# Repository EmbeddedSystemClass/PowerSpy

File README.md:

# PowerSpy

PowerSpy is an IoT device for non-invasive two-phases energy monitoring.

## Features
##### Controller Device / [SoC ESP32 with Xtensa® Dual-Core 32-bit LX6 MPU, Bluetooth 4.2 and Wi-Fi](https://www.espressif.com/sites/default/files/documentation/esp32_datasheet_en.pdf)

##### Low Power Requirements / Does not apply in this project

##### Hardware Project / [Autodesk EAGLE](https://www.autodesk.com/products/eagle/free-download)

##### Firmware Project / [Eclipse IDE](https://www.eclipse.org/eclipseide/)

##### 3D Model Project / [Autodesk Fusion 360](https://www.autodesk.com/products/fusion-360/overview#banner)

## PCB Details

## How to Connect

## Schematic

### Contributing
0. Give this project a :star:
1. Create an issue and describe your idea.
2. [Fork it](https://github.com/TiagoPaulaSilva/PowerSpy/fork).
3. Create your feature branch (`git checkout -b my-new-feature`).
4. Commit your changes (`git commit -a -m "Added feature title"`).
5. Publish the branch (`git push origin my-new-feature`).
6. Create a new pull request.
7. Done! :heavy_check_mark:

### License Information
<br /><span xmlns:dct="http://purl.org/dc/terms/" property="dct:title">PowerSpy</span> by <a xmlns:cc="http://creativecommons.org/ns#" href="https://github.com/TiagoPaulaSilva" property="cc:attributionName" rel="cc:attributionURL">Tiago Silva</a> is licensed under a <a rel="license" href="http://creativecommons.org/licenses/by-sa/4.0/">Creative Commons Attribution-ShareAlike 4.0 International License</a>.<br />Permissions beyond the scope of this license may be available at <a xmlns:cc="http://creativecommons.org/ns#" href="https://twitter.com/tiagopsilvaa" rel="cc:morePermissions">tiagodepaulasilva@gmail.com</a>.

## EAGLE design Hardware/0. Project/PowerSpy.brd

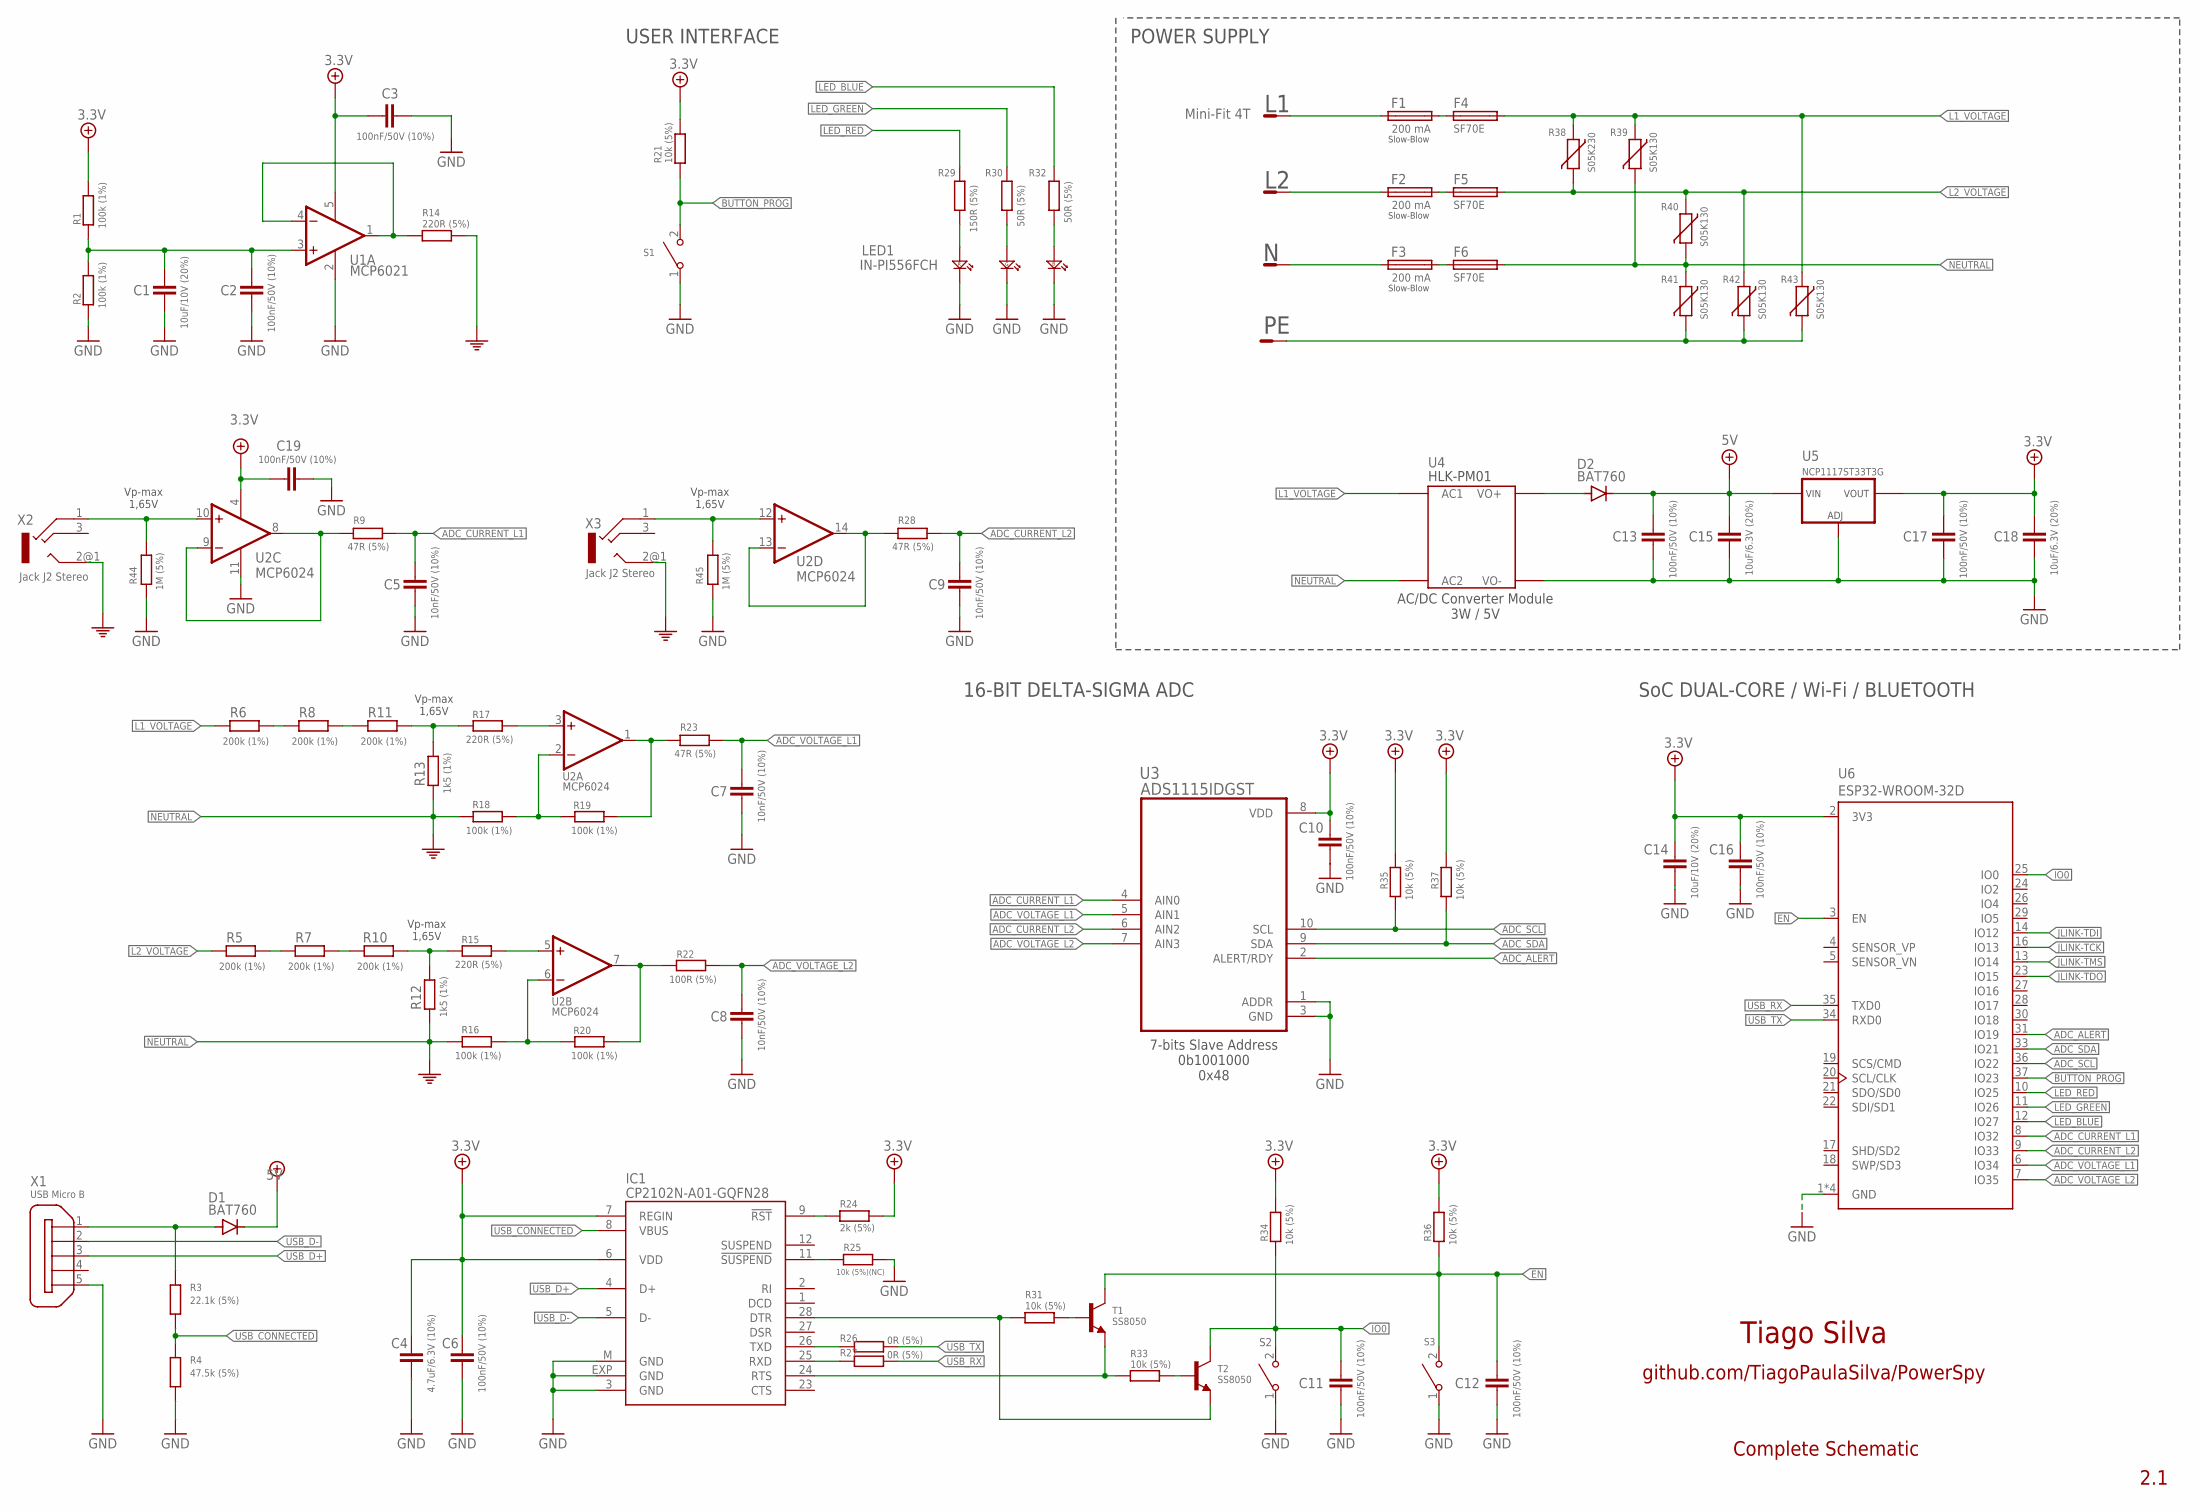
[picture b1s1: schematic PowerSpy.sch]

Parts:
C1, C14: 10uF/10V (20%); C0603K
C2, C3, C6, C10, C11, C12, C13, C16, C17, C19: 100nF/50V (10%); C0603K
C4: 4.7uF/6.3V (10%); C0603K
C5, C7, C8, C9: 10nF/50V (10%); C0603K
C15, C18: 10uF/6.3V (20%); C0603K
CN1: Mini-Fit 4T; 39-30-?04?
D1, D2: BAT760; SOD323-W
F1, F2, F3: 200 mA; QPL
F4, F5, F6: SF70E; LITTLEFUSE
IC1: CP2102N-A01-GQFN28; MLP28
LED1: IN-PI556FCH; INPI556FCH
R1, R2, R16, R18, R19, R20: 100k (1%); R0603
R3: 22.1k (5%); R0603
R4: 47.5k (5%); R0603
R5, R6, R7, R8, R10, R11: 200k (1%); R0603
R9, R23, R28: 47R (5%); R0603
R12, R13: 1k5 (1%); R0603
R14, R15, R17: 220R (5%); R0603
R21, R31, R33, R34, R35, R36, R37: 10k (5%); R0603
R22: 100R (5%); R0603
R24: 2k (5%); R0603
R25: 10k (5%)(NC); R0603
R26, R27: 0R (5%); R0603
R29: 150R (5%); R0603
R30, R32: 50R (5%); R0603
R38: S05K230; S05K11
R39, R40, R41, R42, R43: S05K130; S05K11
R44, R45: 1M (5%); R0603
S1, S2, S3: TL3302AF180QG; 434121050816
T1, T2: SS8050; SOT23
U1: MCP6021; SOT23-5
U2: MCP6024; 14-SOIC
U3: ADS1115IDGST; SOP50P490X110-10N
U4: HLK-PM01
U5: NCP1117ST33T3G; SOT223
U6: ESP32-WROOM-32D; MODULE_ESP32-WROOM-32D
X1: USB Micro B; ZX62D-B-5PA8
X2, X3: Jack J2 Stereo; 1503_07

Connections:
3.3V: C4.1, C6.1, C10.1, C14.1, C16.1, C17.1, C18.1, IC1.6 (VDD), IC1.7 (REGIN), R1.1, R21.1, R24.2, R34.1, R35.1, R36.1, R37.1, U3.8 (VDD), U5.2 (VOUT), U5.4 (VOUT), U6.2 (3V3)
5V: C13.1, C15.1, D1.C, D2.C, U5.3 (VIN)
+4.1V: C3.1, C19.1, U1.5 (V+), U2.4 (V+)
ADC_ALERT: U3.2 (ALERT/RDY), U6.31 (IO19)
ADC_CURRENT_L1: C5.1, R9.1, U3.4 (AIN0), U6.8 (IO32)
ADC_CURRENT_L2: C9.1, R28.1, U3.6 (AIN2), U6.9 (IO33)
ADC_SCL: R35.2, U3.10 (SCL), U6.36 (IO22)
ADC_SDA: R37.2, U3.9 (SDA), U6.33 (IO21)
ADC_VOLTAGE_L1: C7.1, R23.1, U3.5 (AIN1), U6.6 (IO34)
ADC_VOLTAGE_L2: C8.1, R22.1, U3.7 (AIN3), U6.7 (IO35)
BUTTON_PROG: R21.2, S1.2, U6.37 (IO23)
DTR: IC1.28 (DTR), R31.2, T2.2 (E)
EN: C12.1, R36.2, S3.2, T1.3 (C), U6.3 (EN)
GND: C1.2, C2.2, C3.2, C4.2, C5.2, C6.2, C7.2, C8.2, C9.2, C10.2, C11.2, C12.2, C13.2, C14.2, C15.2, C16.2, C17.2, C18.2, C19.2, IC1.3 (GND), IC1.EXP (GND), IC1.M (GND), LED1.4 (KB4), LED1.5 (KG6), LED1.6 (KR5), R2.2, R4.1, R25.1, R44.2, R45.2, S1.1, S2.1, S3.1, U1.2 (V-), U2.11 (V-), U3.1 (ADDR), U3.3 (GND), U4.P$3 (VO-), U5.1 (GND), U6.1 (GND), U6.15 (GND), U6.38 (GND), U6.39 (GND), X1.5
IO0: C11.1, R34.2, S2.2, T2.3 (C), U6.25 (IO0)
JLINK-TCK: U6.16 (IO13)
JLINK-TDI: U6.14 (IO12)
JLINK-TDO: U6.23 (IO15)
JLINK-TMS: U6.13 (IO14)
L1_VOLTAGE: F4.2, R6.1, R38.1, R39.1, R43.1, U4.P$1 (AC1)
L2_VOLTAGE: F5.2, R5.1, R38.2, R40.1, R42.1
LED_BLUE: R32.1, U6.12 (IO27)
LED_GREEN: R30.1, U6.11 (IO26)
LED_RED: R29.1, U6.10 (IO25)
unnamed: IC1.11 (!SUSPEND), R25.2
unnamed: IC1.9 (!RST), R24.1
unnamed: LED1.2 (AR2), R29.2
unnamed: F1.1, F4.1
unnamed: R33.1, T2.1 (B)
unnamed: D2.A, U4.P$4 (VO+)
unnamed: R31.1, T1.1 (B)
unnamed: IC1.26 (TXD), R26.2
unnamed: F2.1, F5.1
unnamed: IC1.25 (RXD), R27.2
unnamed: R9.2, U2.8 (OUT), U2.9 (-IN)
unnamed: R8.2, R11.1
unnamed: R14.2, U1.1 (OUT), U1.4 (-IN)
unnamed: C1.1, C2.1, R1.2, R2.1, U1.3 (+IN)
unnamed: R19.1, R23.2, U2.1 (OUT)
unnamed: R10.2, R12.1, R15.2
unnamed: F3.1, F6.1
unnamed: CN1.4, R41.2, R42.2, R43.2
unnamed: R6.2, R8.1
unnamed: R20.1, R22.2, U2.7 (OUT)
unnamed: LED1.1 (AG1), R30.2
unnamed: R28.2, U2.13 (-IN), U2.14 (OUT)
unnamed: CN1.1, F1.2
unnamed: CN1.2, F2.2
unnamed: CN1.3, F3.2
unnamed: LED1.3 (AB3), R32.2
unnamed: R7.2, R10.1
unnamed: R5.2, R7.1
unnamed: R18.1, R19.2, U2.2 (-IN)
unnamed: R11.2, R13.1, R17.2
unnamed: R17.1, U2.3 (+IN)
unnamed: R16.1, R20.2, U2.6 (-IN)
unnamed: R15.1, U2.5 (+IN)
unnamed: R44.1, U2.10 (+IN), X2.1
unnamed: R45.1, U2.12 (+IN), X3.1
NEUTRAL: F6.2, R12.2, R13.2, R14.1, R16.2, R18.2, R39.2, R40.2, R41.1, U4.P$2 (AC2), X3.2@1 (2)
PE: X2.2@1 (2)
RTS: IC1.24 (RTS), R33.2, T1.2 (E)
USB_CONNECTED: IC1.8 (VBUS), R3.1, R4.2
USB_D+: IC1.4 (D+), X1.3
USB_D-: IC1.5 (D-), X1.2
USB_RX: R27.1, U6.35 (TXD0)
USB_TX: R26.1, U6.34 (RXD0)
VUSB: D1.A, R3.2, X1.1

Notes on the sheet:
Tiago Silva
github.com/TiagoPaulaSilva/PowerSpy
2.1
Complete Schematic
AC/DC Converter Module 3W / 5V
POWER SUPPLY
Slow-Blow
16-BIT DELTA-SIGMA ADC
SoC DUAL-CORE / Wi-Fi / BLUETOOTH
USER INTERFACE
Vp-max 1,65V
7-bits Slave Address 0b1001000 0x48

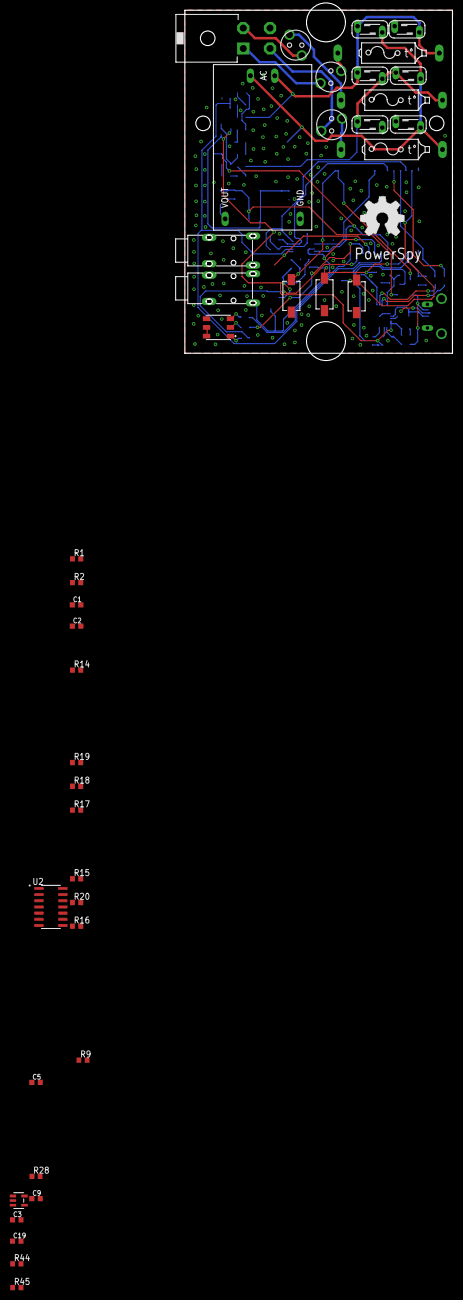
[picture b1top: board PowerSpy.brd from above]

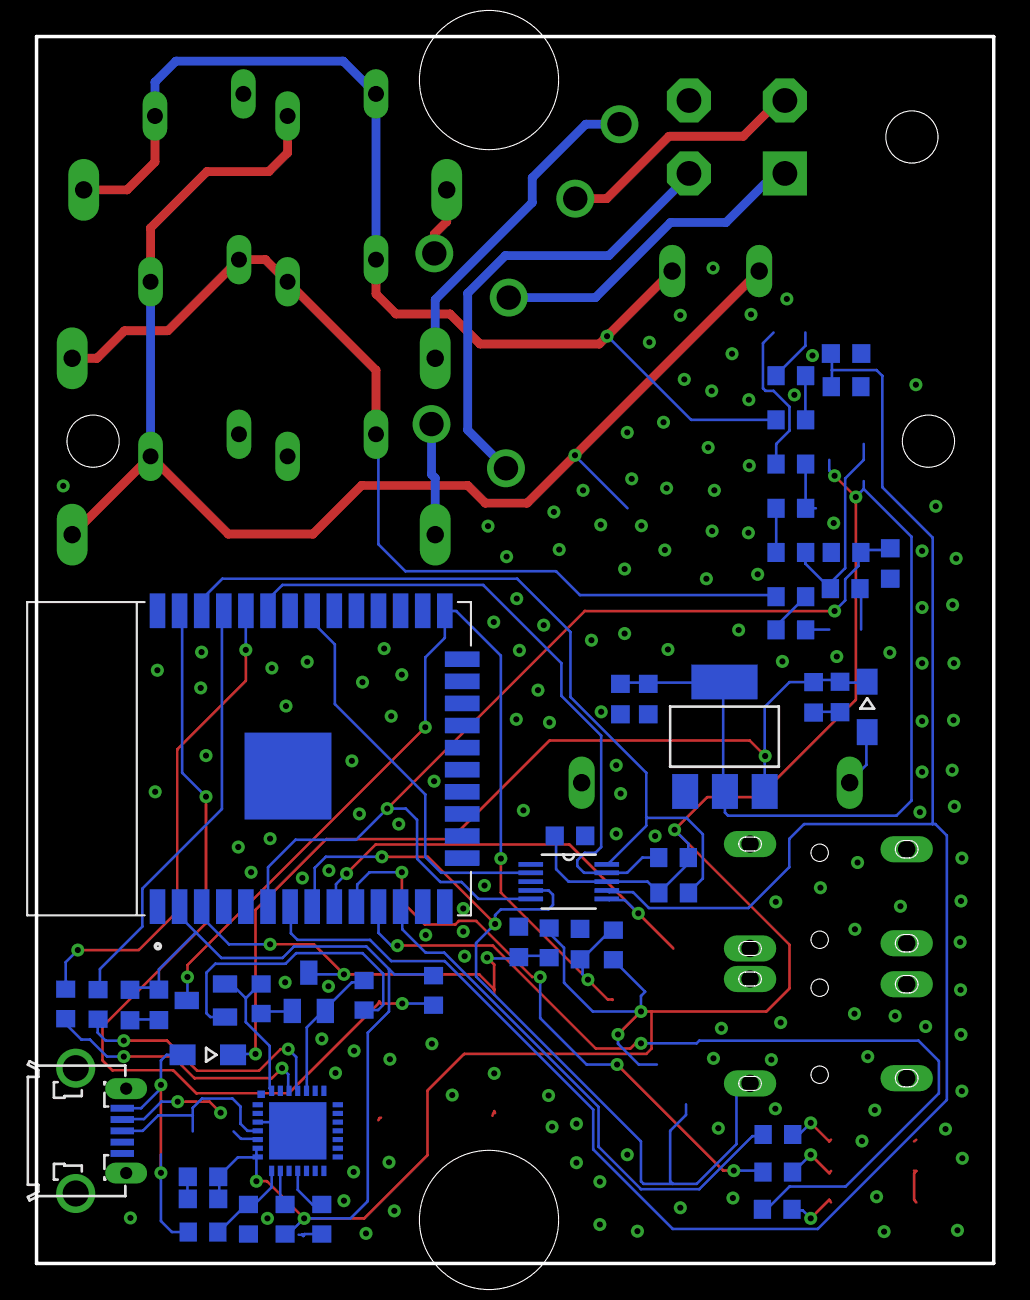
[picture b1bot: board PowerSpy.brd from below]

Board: 2 copper layers, 55.0 x 70.5 mm, 89 parts (48 on the bottom side), 63 nets.

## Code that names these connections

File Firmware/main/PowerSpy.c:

/* 			LIBRARIES DECLARATION 			*/
#include <stdio.h>

#include "freertos/FreeRTOS.h"
#include "freertos/task.h"

#include "esp_system.h"
#include "sdkconfig.h"
#include "esp_log.h"

#include "driver/gpio.h"

#include <ads111x.h>
#include <string.h>


/* 			HARDWARE PINS DEFINITIONS 			*/

//User's Interface
#define LED_RED_PIN 			25
#define LED_GREEEN_PIN  		26
#define LED_BLUE_PIN			27
#define BUTTON_PROG_PIN			23

//Analog Front-End Interface
#define ADC_CURRENT_L1_PIN 		32
#define ADC_CURRENT_L2_PIN 		33
#define ADC_VOLTAGE_L1_PIN 		34
#define ADC_VOLTAGE_L2_PIN 		35

#define ADC_TO_I2C_ALERT		19
#define ADC_TO_I2C_SDA			21
#define ADC_TO_I2C_SCL			22

#define DEV_COUNT 1

#define I2C_PORT 0


#define SDA_GPIO 21
#define SCL_GPIO 22


#define GAIN ADS111X_GAIN_4V096 // +-4.096V


// I2C addresses
static const uint8_t addr[DEV_COUNT] = {
    ADS111X_ADDR_GND,

};

// Descriptors
static i2c_dev_t devices[DEV_COUNT];

// Gain value
static float gain_val;



void ads111x_test(void *pvParamters) {
    gain_val = ads111x_gain_values[GAIN];

    // Setup ICs
	ESP_ERROR_CHECK(ads111x_init_desc(&devices[0], addr[0], I2C_PORT, SDA_GPIO, SCL_GPIO));

	ESP_ERROR_CHECK(ads111x_set_mode(&devices[0], ADS111X_MODE_CONTUNOUS));    // Continuous conversion mode
	ESP_ERROR_CHECK(ads111x_set_data_rate(&devices[0], ADS111X_DATA_RATE_8)); // 32 samples per second
	ESP_ERROR_CHECK(ads111x_set_input_mux(&devices[0], ADS111X_MUX_1_GND));    // positive = AIN0, negative = GND
	ESP_ERROR_CHECK(ads111x_set_gain(&devices[0], GAIN));


    while (1)
    {
	   // wait for conversion end
		bool busy;
		do
		{
			ads111x_is_busy(&devices[0], &busy);
		}
		while (busy);

		// Read result
		int16_t raw = 0;
		if (ads111x_get_value(&devices[0], &raw) == ESP_OK)
		{
			float voltage = (4.096 / ADS111X_MAX_VALUE * raw) * 38;
			//printf("[%u] Raw ADC value: %d, voltage: %.04f volts\n", 0, raw, voltage);
			printf("%.04f\n", voltage);
		}
		else
			printf("[%u] Cannot read ADC value\n", 0);



        vTaskDelay(10 / portTICK_PERIOD_MS);
    }
}

void led_controller(void *pvParameter) {
	while(1)
	{
		gpio_set_level(LED_GREEEN_PIN, 1);
		vTaskDelay(1000 / portTICK_PERIOD_MS);
		gpio_set_level(LED_GREEEN_PIN, 0);
		vTaskDelay(1000 / portTICK_PERIOD_MS);
	}
}

void app_main() {
	gpio_pad_select_gpio(LED_RED_PIN);
	gpio_pad_select_gpio(LED_GREEEN_PIN);
	gpio_pad_select_gpio(LED_BLUE_PIN);
	gpio_pad_select_gpio(BUTTON_PROG_PIN);

	gpio_set_direction(LED_RED_PIN,    GPIO_MODE_OUTPUT);
	gpio_set_direction(LED_GREEEN_PIN, GPIO_MODE_OUTPUT);
	gpio_set_direction(LED_BLUE_PIN,   GPIO_MODE_OUTPUT);
	gpio_set_direction(BUTTON_PROG_PIN, GPIO_MODE_INPUT);

	gpio_set_level(LED_RED_PIN, 0);
	gpio_set_level(LED_GREEEN_PIN, 0);
	gpio_set_level(LED_BLUE_PIN, 0);

    ESP_ERROR_CHECK(i2cdev_init());

    memset(devices, 0, sizeof(devices));

    xTaskCreatePinnedToCore(&ads111x_test, "ads111x_test", configMINIMAL_STACK_SIZE * 8, NULL, 5, NULL, PRO_CPU_NUM);
    xTaskCreate(&led_controller, "led_controller", 2048, NULL, 1, NULL);
}

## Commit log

2019-07-22 Readme updated
2019-07-22 .gitattributes file added
2019-07-23 Schematic updated
2019-07-24 Schematic done. PCB layout started
2019-07-26 Schematic done. PCB layout almost done.
2019-07-26 PCB layout finished
2019-07-27 3D Model's PCB Added
2019-11-16 New images added
2020-01-27 2.0 PCB created
    - Board dimensions resize to match with PB075 Patola case.
2020-01-29 VCC/2 set point added to voltage phase measure channel (WIP)
2020-01-29 Calcs details improved
2020-01-29 New analog front-end design for voltage measurement
2020-01-29 Calcs and values updated for the new AFE approach
2020-01-31 Schematic parts renumbered
2020-02-02 First HW+FW test
2020-02-04 New firmware project from Elipse IDE
2020-02-05 New project configs
2020-02-05 New datasheet added
2020-02-06 Another new and better AFE approach
2020-02-06 CP2102 uptadeted for a better revision datasheet
2020-02-06 Schematic parts renumbered
2020-02-06 Schematic image preview updated to 2.0 project
2020-02-06 New firmware project structure
2020-02-06 Minor improvements
2020-02-06 SoC Datasheets updated
2020-02-06 ADS1115 7-bits slave address added to schematic
2020-02-07 GPIO pins tests and working OK
2020-02-07 PCB Details image updated
2020-02-08 Setup the FreeRTOS to run on first core
2020-02-08 FreeRTOS code architecture applied
2020-02-09 Native I2C attempt
2020-02-09 I2C Working on FreeRTOS
2020-02-12 Pull-down resistor added to current AFE
2020-02-13 Schematic image preview updated
2020-02-14 L1 voltage measurement working with LED blinky
2020-02-15 WIP voltage waveform reconstruction
2020-02-19 ESP32 JLINK Pins added

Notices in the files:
parts and their libraries:
con-molex-mini-fit: Copyright (C) 2011, Bob Starr
